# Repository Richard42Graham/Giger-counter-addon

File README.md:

# Giger-counter-addon

this is a addon board for a giger counter i got at a workshop.

its desigend as a addon bord.

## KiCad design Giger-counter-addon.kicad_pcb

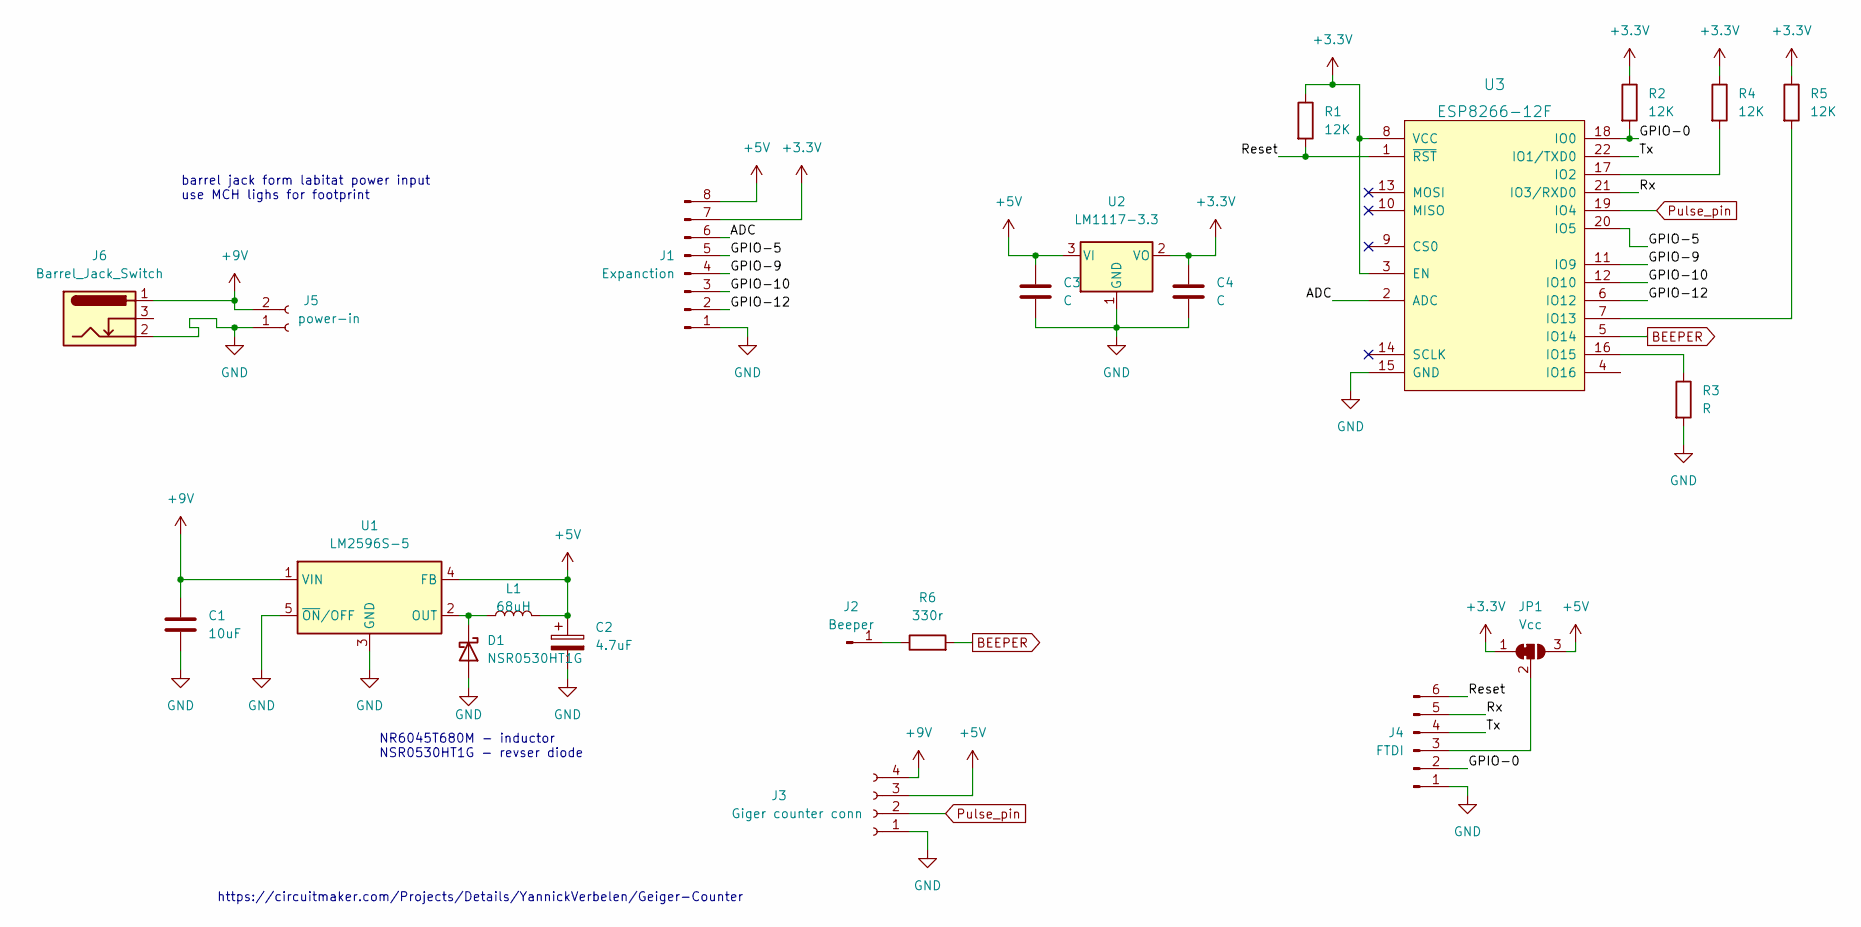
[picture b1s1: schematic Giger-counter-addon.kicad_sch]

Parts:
C1: 10uF; C_0805_2012Metric
C2: 4.7uF; C_0805_2012Metric
C3, C4: C; C_0805_2012Metric
D1: NSR0530HT1G; D_SOD-323
J1: Expanction; PinSocket_2x04_P2.54mm_Vertical
J2: Beeper; PinSocket_1x01_P2.54mm_Vertical
J3: Giger counter conn; PinSocket_1x04_P2.54mm_Vertical
J4: FTDI; PinSocket_1x06_P2.54mm_Vertical
J5: power-in; PinSocket_1x02_P2.54mm_Vertical
J6: Barrel_Jack_Switch; BarrelJack_GCT_DCJ200-10-A_Horizontal
JP1: Vcc; SolderJumper-3_P1.3mm_Bridged2Bar12_RoundedPad1.0x1.5mm
L1: 68uH; L_Taiyo-Yuden_NR-60xx_HandSoldering; Part number NR6045T680M
R1, R2, R4, R5: 12K; R_0603_1608Metric
R3: R; R_0603_1608Metric
R6: 330r; R_0603_1608Metric
U1: LM2596S-5; TO-263-5_TabPin3
U2: LM1117-3.3; SOT-223-3_TabPin2
U3: ESP8266-12F; ESP8266-13F

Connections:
+3.3V: C4.1, J1.7, JP1.1 (A), R1.1, R2.1, R4.1, R5.1, U2.2 (VO), U3.3 (EN), U3.8 (VCC)
+5V: C2.1, C3.1, J1.8, J3.3, JP1.3 (B), L1.2, U1.4 (FB), U2.3 (VI)
+9V: C1.1, J3.4, J5.2, J6.1, U1.1 (VIN)
/ADC: J1.6, U3.2 (ADC)
/GPIO-0: J4.2, R2.2, U3.18 (IO0)
/GPIO-5: J1.5, U3.20 (IO5)
/GPIO-9: J1.4, U3.11 (IO9)
/GPIO-10: J1.3, U3.12 (IO10)
/GPIO-12: J1.2, U3.6 (IO12)
/Reset: J4.6, R1.2, U3.1 (~RST)
/Rx: J4.5, U3.21 (IO3/RXD0)
/Tx: J4.4, U3.22 (IO1/TXD0)
BEEPER: R6.2, U3.5 (IO14)
GND: C1.2, C2.2, C3.2, C4.2, D1.2 (A), J1.1, J3.1, J4.1, J5.1, J6.2, R3.2, U1.3 (GND), U1.5 (~ON/OFF), U2.1 (GND), U3.15 (GND)
unnamed: D1.1 (K), L1.1, U1.2 (OUT)
unnamed: J2.1, R6.1
unnamed: J4.3, JP1.2 (C)
unnamed: R3.1, U3.16 (IO15)
unnamed: R4.2, U3.17 (IO2)
unnamed: R5.2, U3.7 (IO13)
Pulse_pin: J3.2, U3.19 (IO4)

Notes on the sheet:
NR6045T680M - inductor NSR0530HT1G - revser diode
https://circuitmaker.com/Projects/Details/YannickVerbelen/Geiger-Counter
barrel jack form labitat power input use MCH lighs for footprint

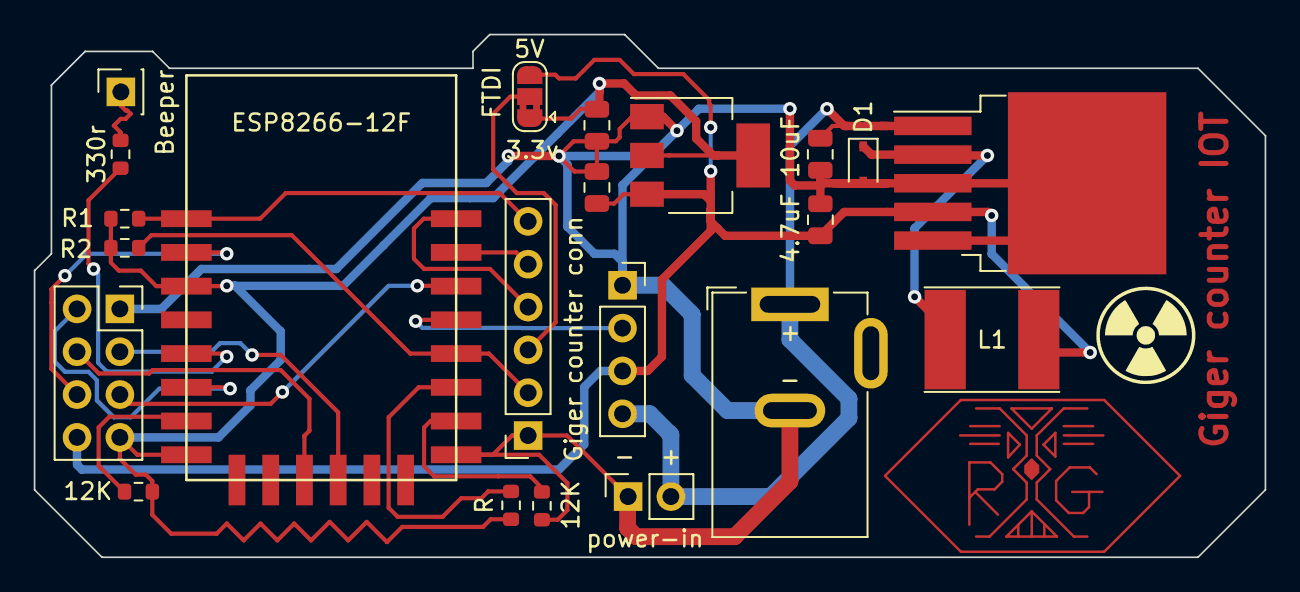
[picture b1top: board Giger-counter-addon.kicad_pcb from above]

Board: 2 copper layers, 73.0 x 31.0 mm, 22 parts (0 on the bottom side), 21 nets.

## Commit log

2023-08-05 inital working release of the giger counter bourd.
2023-08-05 cleaned up some notes
2023-08-06 added software and libary links for it
